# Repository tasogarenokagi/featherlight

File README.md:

LED medallion with 9-DOF motion sensing.

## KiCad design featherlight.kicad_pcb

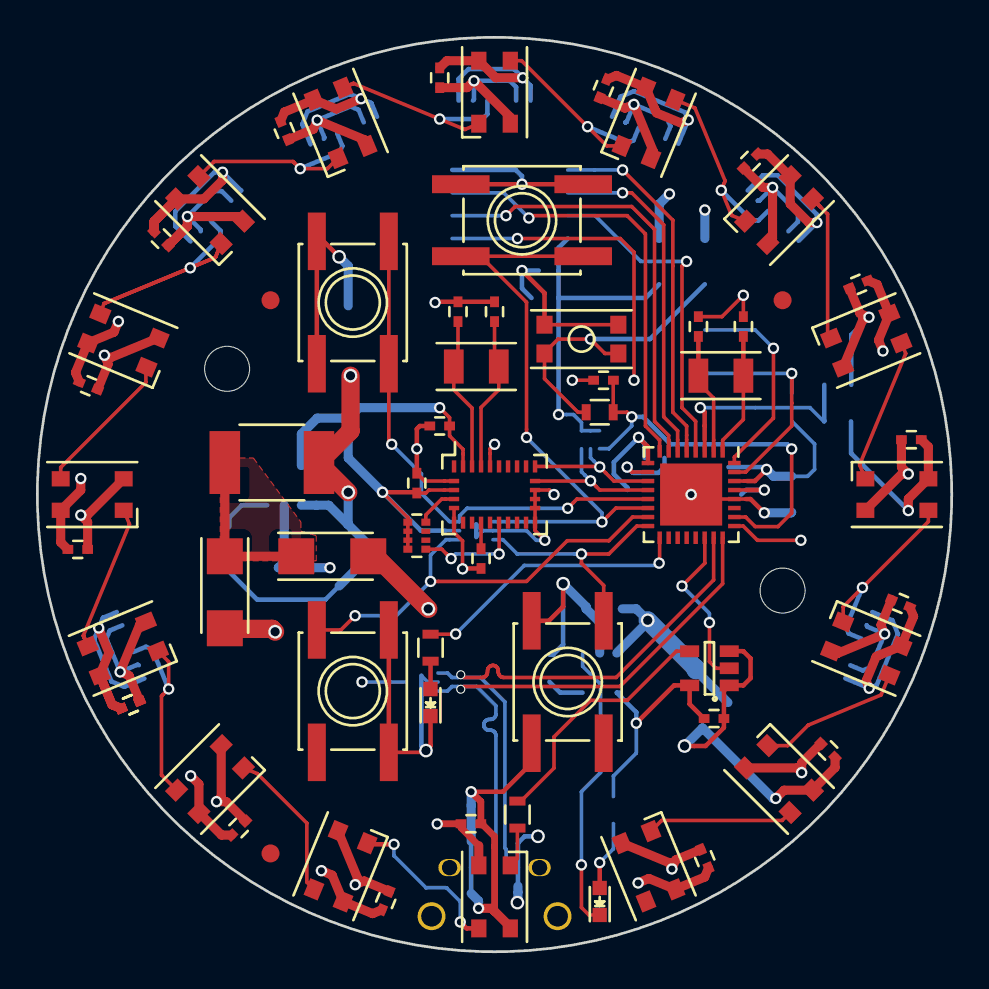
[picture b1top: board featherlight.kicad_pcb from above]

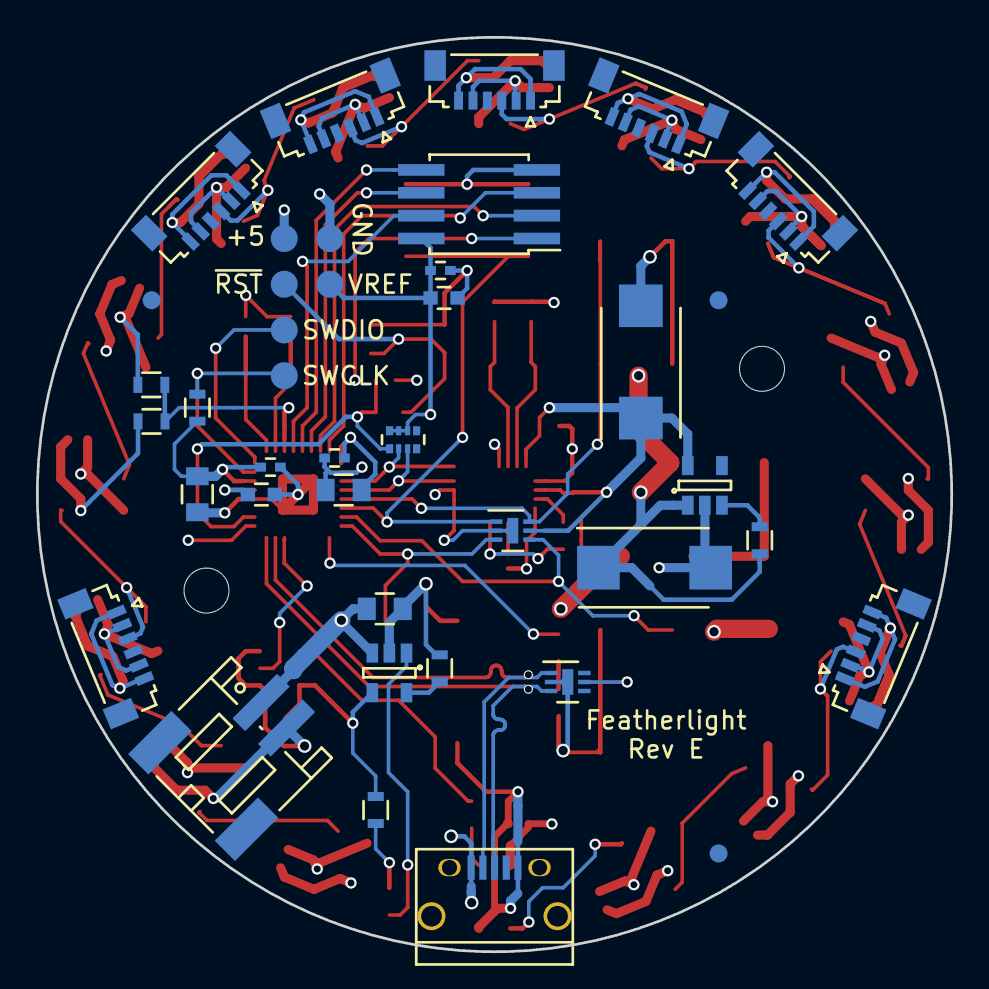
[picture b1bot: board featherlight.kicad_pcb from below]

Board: 4 copper layers, 50.8 x 50.8 mm, 106 parts (40 on the bottom side), 57 nets.

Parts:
C1, C2, C10, C11: 22 pF; C_0402
C3, C4, C7, C8, C9, C12, C13, C15, C16, C17, C18, C19, C20, C21, C22, C22#2, C23, C24, C25, C26, C27, C28, C29, C30, C35: 0.1 uF; C_0402
C5, C6, C33: 10 uF; C_0805
C14, C34: 1 uF; C_0603
C31, C32: 220 uF; TantalC_SizeD_EIA-7343_Reflow
D1, D2, D3, D4, D5, D6, D7, D8, D9, D10, D11, D12, D13, D14, D15, D16: SK6812MINI; LED_SK6812MINI-PLCC4
D19, D23: DRTR5V0U4LP16; DFN-6-1EP_2x2mm_Pitch0.5mm
D20, D24: MBRA210LT3G; DO-214AC
D21: Green; LED_0603
D22: Red; LED_0603
F1: FUSE; 1812_PTC
FID1, FID2, FID3, FID4, FID5, FID6: Fiducial; Fiducial_1mm_Dia_2.54mm_Outer_CopperTop
HOLE1, HOLE2: Fiducial; MountingHole_2.5mm
P1: USB_OTG; USB_Micro-B
P2: CONN_01X02; JST_PH_S2B-PH-SM4-TB_02x2.00mm_Angled
P3, P4, P5, P6, P7, P8: CONN_01X01; Measurement_Point_Round-SMD-Pad_Small
P11, P12, P13, P14, P15, P16, P17: CONN_01X06; JST_SUR_SM06B-SURS-TF_06x0.80mm_Angled
R2, R7, R12: 470; R_0603
R3, R4: 1 K; R_0603
R10, R11, R13: 100 K; R_0603
R14: 10 K; R_0603
RN1, RN2: 10 K; R_Array_Convex_4x0402
SW1: Button; KMR2_switch
SW2, SW3, SW4, SW5: Button; SW_SPST_EVQQ2
U1: BNO055; LGA-28
U2: SAMD21E18A-M; QFN-32-1EP_5x5mm_Pitch0.5mm
U3: 74AHCT1G125; SOT-23-5
U4: AP2112; SOT-23-5
U5: MCP73831; SOT-23-5
U6: 16 Mb SPI Flash; SOIC-8_Universal_Pitch1.27mm
Y1, Y2: 32.768 KHz; Crystal_SMD_3215_2Pads

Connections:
+3V3: C3.1, C4.2, C5.1, C6.2, C7.1, C8.2, C32.1, C34.1, C35.1, D23.5, P8.1, R4.1, RN1.6, RN1.7, RN1.8, RN2.1, RN2.2, RN2.3, RN2.4, U1.3, U1.28, U2.9, U2.30, U4.5, U6.8
+BATT: C33.2, D20.2, P2.1, U5.3
/LED Array/D1D0: D1.1, D2.3
/LED Array/D2DO: D2.1, D3.3
/LED Array/D3DO: D3.1, D4.3, P11.3
/LED Array/D4DO: D4.1, D5.3
/LED Array/D5DO: D5.1, D6.3
/LED Array/D6DO: D6.1, D7.3, P12.3
/LED Array/D7DO: D7.1, D8.3, P13.3
/LED Array/D8DO: D8.1, D9.3, P14.3
/LED Array/D9DO: D9.1, D10.3, P15.3
/LED Array/D10DO: D10.1, D11.3, P16.3
/LED Array/D11DO: D11.1, D12.3
/LED Array/D13DO: D13.1, D14.3, P17.3
/LED Array/D14DO: D14.1, D15.3
/LED Array/D15DO: D15.1, D16.3
/MCU + IMU/ATMEL_RESET: C9.1, R2.1, RN1.1, U2.26
/MCU + IMU/BNO_BOOTLOAD: RN2.8, U1.4
/MCU + IMU/BNO_RESET: RN2.5, U1.11
/MCU + IMU/LV_LED_control_stream: U2.22, U3.2
/MCU + IMU/MISO: U2.7, U6.2
/MCU + IMU/MOSI: U2.5, U6.5
/MCU + IMU/SCL: RN1.3, U1.19, U2.12
/MCU + IMU/SCLK: U2.6, U6.6
/MCU + IMU/SDA: RN1.2, U1.20, U2.11
/MCU + IMU/~CS~: U2.25, U6.1
/MCU + IMU/~HOLD~: U2.4, U6.7
/MCU + IMU/~WP~: U2.8, U6.3
/Power Regulation & Distribution/VFUSE: D20.1, D24.1, F1.1
/Power Regulation & Distribution/VUSB: D19.5, D24.2, P1.1
D+: D19.3, P1.3, U2.24
D-: D19.1, P1.2, U2.23
GND: C1.1, C2.1, C3.2, C4.1, C5.2, C6.1, C7.2, C8.1, C9.2, C10.1, C11.1, C12.2, C13.2, C14.2, C15.2, C16.2, C17.2, C18.2, C19.2, C20.2, C21.2, C22.2, C22#2.2, C23.2, C24.2, C25.2, C26.2, C27.2, C28.2, C29.2, C30.2, C31.2, C32.2, C33.1, C34.2, C35.2, D1.2, D2.2, D3.2, D4.2, D5.2, D6.2, D7.2, D8.2, D9.2, D10.2, D11.2, D12.2, D13.2, D14.2, D15.2, D16.2, D19.2, D19.7, D22.1, D23.2, D23.7, P1.5, P1.6, P2.2, P7.1, P11.1, P11.6, P12.1, P12.6, P13.1, P13.6, P14.1, P14.6, P15.1, P15.6, P16.1, P16.6, P17.1, P17.6, R13.1, R14.2, SW1.1, SW2.1, SW3.1, SW4.1, SW5.1, U1.2, U1.5, U1.6, U1.15, U1.16, U1.17, U1.18, U1.25, U2.10, U2.28, U2.33, U3.1, U3.3, U4.2, U5.2, U6.4
LED_control_stream: R7.2, U3.4
LL_BUTTON: D23.4, SW4.2, U2.15
LR_BUTTON: D23.3, SW5.2, U2.16
unnamed: C1.2, U2.1, Y1.1
unnamed: C2.2, U2.2, Y1.2
unnamed: C10.2, U1.26, Y2.1
unnamed: C11.2, U1.27, Y2.2
unnamed: C12.1, U1.9
unnamed: C14.1, U2.29
unnamed: D1.3, R7.1
unnamed: D12.1, D13.3
unnamed: D21.1, U5.1
unnamed: D21.2, R12.2
unnamed: D22.2, R3.1
unnamed: R3.2, U2.17
unnamed: R10.1, U4.3
unnamed: R14.1, U5.5
SWCLK: P3.1, R4.2, U2.31
SWDIO: P4.1, U2.32
UL_BUTTON: D23.6, SW2.2, U2.13
UR_BUTTON: D23.1, SW3.2, U2.14
VDD: C13.1, C15.1, C16.1, C17.1, C18.1, C19.1, C20.1, C21.1, C22.1, C22#2.1, C23.1, C24.1, C25.1, C26.1, C27.1, C28.1, C29.1, C30.1, C31.1, D1.4, D2.4, D3.4, D4.4, D5.4, D6.4, D7.4, D8.4, D9.4, D10.4, D11.4, D12.4, D13.4, D14.4, D15.4, D16.4, F1.2, P6.1, P11.2, P11.5, P12.2, P12.5, P13.2, P13.5, P14.2, P14.5, P15.2, P15.5, P16.2, P16.5, P17.2, P17.5, R10.2, R11.2, R12.1, U3.5, U4.1, U5.4
VDD_MON: R11.1, R13.2, U2.3
~RST~: P5.1, R2.2, SW1.2

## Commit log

2016-08-26 initial file import
2016-08-26 Gerber export for prototype rev-A.
2016-08-30 Added part BOM metadata.
2016-09-02 Component changes to reduce BOM cost.
    -Swap SAMD21 package to 48-QFN.
    -Swap Tantalum power caps for Aluminum Polymer.
2016-09-04 Prepare for github export.
    -Added README.md
    -Added LICENSE.md
    -Exported footprints.
2016-09-08 Fixed a few small issues with the library components revealed by DRC.
    Why they didn't show up until now is a mystery.
2016-09-08 Further development work while waiting for the first prototypes to come back.
    -Moved to 4 layer board because the power routing got to be too much of a headache.
    -Run all power through a PTC fuse.
    -Added a voltage divider to allow the MCU to monitor bus voltage.
    -Added JST-2 connector and battery circuitry to permit powering from lipo cells. Feeds VDD via a diode to avoid bad things happening. Intended to work with Adafruit's packs.
    -Added 4 push buttons to form a user interface.
    -Removed external pull up resistor on reset line. MCU has internal pull ups.
2016-09-08 Propagate component MSL data back from BOM spreadsheet.
2016-09-08 Tweaked trace routing to remove several vias.
    Expanded the copper pour connecting 3.3V regulator to power plane.
    Removed placeholder MDBT40 footprint. I want to see if the buttons are enough of a UI that bluetooth is no longer necessary.
2016-09-09 Changed PTH on the USB footprint to circular drills since Oshpark cannot into slots.
2016-09-11 Improper board size required full PCB redesign.
    The rev A PCBs were far bigger than intended (target diameter was used as radius when laying it out).
    Removed lipo circuit while reworking layout; will try to add it back in later.
    Moved USB port to very edge of board to permit cable access.
    Added +5V and ground contacts to ISP pads.
    Swapped down to SAMD21E MCU for space reasons.
    Removed connectors for space reasons. Maybe they'll fit on the bottom?
2016-09-11 Linked appropriate or placeholder 3D models to custom footprints.
2016-09-11 Re-added lipo circuit.
2016-09-11 Trying out a 2 inch diameter disk.
2016-09-12 Added MCU reset to SWD pads.
2016-09-13 I have greatly misunderstood the function of VDDCore on the MCU. orz.
    Added additional bypass caps for the MCU and changed the battery bypass cap for BOM commonality.
2016-09-13 Reenumerated all components.
2016-09-14 Added mounting holes and two candidates for fingerlight connectors.
2016-09-15 Swapped UI buttons to EVQQ2 and rearranged board to fit.
2016-09-15 Gerber export for Rev B.
2016-09-15 Always run DRC before commiting.
2016-09-15 Gerber export for 2 inch Rev B.
2016-09-16 Dimensioned PCB and location of mounting holes.
2016-09-16 updated git ignore.
2016-09-16 Redid dimensioning after trying to create a mechanical model.
2016-09-18 cleaned up VUSB trace on the back layer.
2016-09-19 Swapped BOM fields on UI buttons to Panasonic EVQQ2 switches.
2016-09-19 Moved 2nd resistor in VDD voltage divider to top layer because I can and it deletes a via.
2016-09-27 Added USB plated through holes to paste layers.
2016-09-27 Reexport following changes.
2016-09-27 Exported paste layers as DXF and composited them with openscad.
2016-10-06 Rerouted serpentine ground trace on neopixel #1
2016-10-06 Bumped revision to rev C.
2016-10-09 10000 pF is not 0.1 uF. Fixed all the screwed up caps.
2016-11-24 Swapped stencil sides to match paste jig.
2016-11-25 reimported project.
2016-11-25 Remove uneeded track found during gerber review.
2016-11-25 Adjusted micro USB footprint so the PTH are not on the front paste layer.
2016-11-26 Reduced solder paste ratio to try and address solder bridging issues.
2016-11-27 Critical failure: EP on SAMD21 is tied to ground. orz.
2016-11-27 Addressed several todo items while working towards rev C tape out.
    *Tweaked fill zone settings.
    *Tweaked design rules to permit use of a faster PCB house.
    *Removed FFC connectors since they were found wanting vs the JST SUR connectors.
    *Replaced cluster of 10 K resistors with a packed array.
2016-11-28 Addressed several todo items while working towards rev C tape out.
    *Added additional fingerlight connectors to make the design ambidextrous.
    *Moved programming pads and added a 3.3V Vref pad.
    *Added a SPI flash chip because micropython might be cool.
    *Added ESD protection to the UI buttons and adjusted schematic to allow use of a different component.
    *Added isolation diode on Vusb, and moved Vusb trace to internal layer.
2016-11-28 Trace cleanup noticed while reviewing gerbers.
2016-11-28 Rev C gerbers and stencil.
2016-12-10 Somehow I deleted the mounting holes while working on rev C.
    Had to move UL button and VDD power LED to add them back in at a new position.
2016-12-10 Bumped to rev D.
2016-12-11 Added stencil supports to Eco layers and re-dimensioned the mounting holes.
2016-12-11 Added stencil supports to Eco layers.
2016-12-18 Added border cuts to stencil.scad and regenerated stencil file.
2016-12-18 Rescaled power diode 3D models, and adjusted support pillar after jig fabrication issues.
2016-12-23 Adjusted support pillar after jig fabrication issues.
2016-12-26 Center supports on Eco1.user layer were causing issues when trying to stencil the rear components, so they're gone.
2017-01-02 Border cuts ended up being a bad idea; disabled them.
    Cutting the stencil out of the rest of the sheet meant solder paste went everywhere.
2017-01-03 Removed trace bodge on USB ESD protection. A solder bridge will work for the few remaining components.
2017-01-03 Deleted power rail LEDs.
2017-01-03 Discovered why the mounting holes keep disappearing, so they're on the schematic now.
2017-01-03 Replaced SOIC-8 footprint with one that can accomodate both 3.9mm and 5.3mm component widths.
2017-01-03 Holes are not fiducials (but their schematic graphic is useful.
2017-01-04 Regenerated fill zones.
2017-01-04 Deleted central pillars on Eco1.User support layer.
2017-01-04 Moved enable resistor on regulator to avoid support pillar.
2017-01-04 Moved programming header label due to resized 8-SOIC footprint.
2017-01-04 Changed silkscreen of 220 uF cap to better highlight pin 1 polarity.
2017-01-04 Generated rev D gerbers and stencil.
2017-01-11 Changed pad and mask geometry of BNO055 footprint based on manufacturer guidelines (ref. Handling, soldering & mounting instructions for BNO055).
2017-01-11 Extensive revisions of PCB connecting and near the BNO055 after issues with rev C and finding relevant design notes.
    -Top copper layer below the sensor is now a keep out zone. This required extensive trace rerouting due to all the pins tied to ground.
    -Added pullups to the bootloader and reset pins (they were previously floating). Expect this was the main reason I could never get it to initialize.
    -Added pulldown to I2C address selection pin (it was previously directly connected). It's what Adafruit does and I had an extra lane in the nearby resistor pack.
2017-01-11 Moved USB port inwards slightly after noticing damage to the outer PTH on rev C boards.
2017-01-12 Grounded USB shield after issues with programming MCU over USB.
    The Atmel design notes recommend grounding through an RC filter, but Adafruit ignores it, and that's good enough for me.
2017-01-12 Rotated the power diodes and fuse since the spiralling traces bothered me.
2017-01-12 Regenerated gerbers. Still calling this rev D.
2017-01-12 Bumped mounting holes up to M2.5 (Adafruit again).
2017-01-12 Regenerated gerbers.
2017-01-23 Propagated all jig changes to the Eco* layers.
2017-01-23 Fixed component 3d models after a kicad update.
2017-01-24 Put MCU analog ground and VDD on dedicated vias after reading a bit about analog PCB design.
    http://www.edn.com/design/pc-board/4443239/Properly-ground-your-circuits
2017-01-24 Rev E
2017-01-26 Changed pin types on the TVS array after studying up Electronic Rules Checking.
2017-01-26 Moved via to the side of the internal power trace.
2017-01-26 Reduced global solder mask pullback to 0.05 mm to address solder briding issues on some of the components.
2017-01-26 Standardized on 8 mil width for all non-power MCU traces.
2017-01-26 Added part number and manufacturer to SPI flash component.
2017-01-26 Ran the numbers so USB differential traces are 8 mil wide and spaced 0.5 mm on center.
2017-01-27 Replaced as many thin vias as I could.
    The remainders are the USB data traces and the critial area between MCU and IMU.
2017-01-31 All 0402 components (0.1 uF or 22 pF capacitors) fixed to -5% paste coverage.
2017-01-31 Added fake dowel pad with tuned paste layer parameters.
    Represents the alignment dowel pins when generating stencil gerbers for external fabrication.
2017-02-01 Moved USB port outwards slightly after issues populating it.
    Split the difference between Rev C and Rev D.
2017-03-16 Changed BNO055 I2C address selection from a pull down to a direct ground tie in the hope it will fix the address instability.
2017-07-07 Updated USB port schematic symbol after kicad update.
2018-02-08 Updated schematics to EESchema version 4 file format.
